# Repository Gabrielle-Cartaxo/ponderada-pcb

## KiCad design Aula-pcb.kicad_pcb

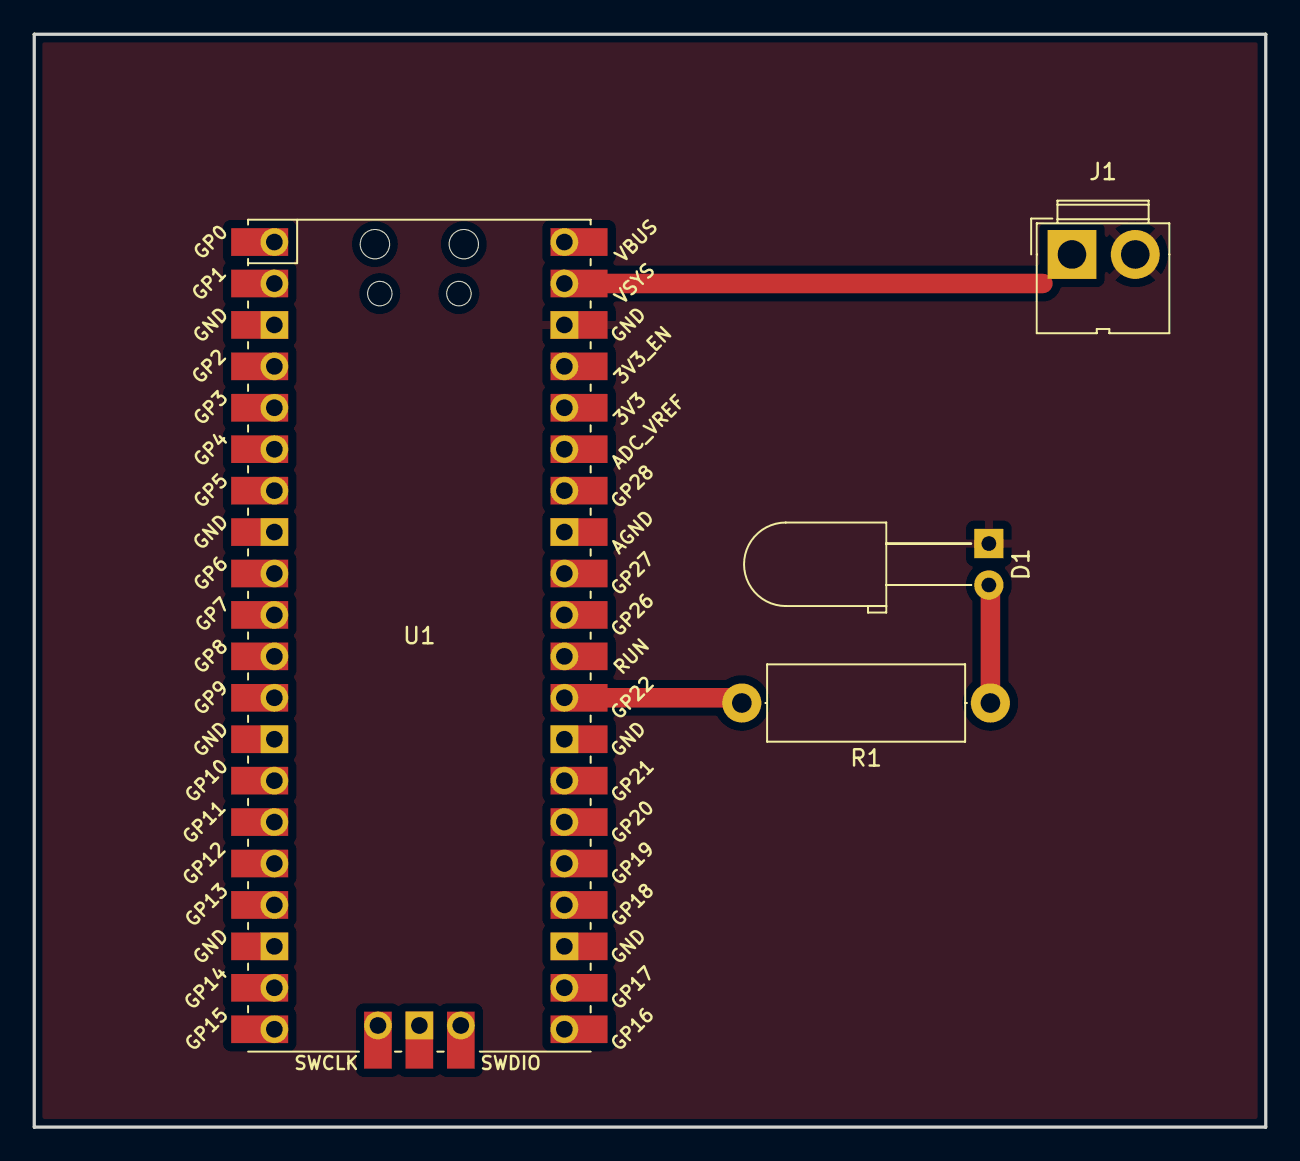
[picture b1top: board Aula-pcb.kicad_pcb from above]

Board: 2 copper layers, 75.5 x 67.0 mm, 4 parts (0 on the bottom side), 4 nets.

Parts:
D1: LED; LED_D5.0mm_Horizontal_O6.35mm_Z9.0mm
J1: Alimentação; JWT_A3963_1x02_P3.96mm_Vertical
R1: 220; R_Axial_DIN0414_L11.9mm_D4.5mm_P15.24mm_Horizontal
U1: Pico; RPi_Pico_SMD_TH

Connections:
GND: D1.1 (K), J1.2, U1.38 (GND)
unnamed: D1.2 (A), R1.1
unnamed: R1.2, U1.29 (GPIO22)
VCC: J1.1, U1.39 (VSYS)

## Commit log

2024-04-01 ponderada
